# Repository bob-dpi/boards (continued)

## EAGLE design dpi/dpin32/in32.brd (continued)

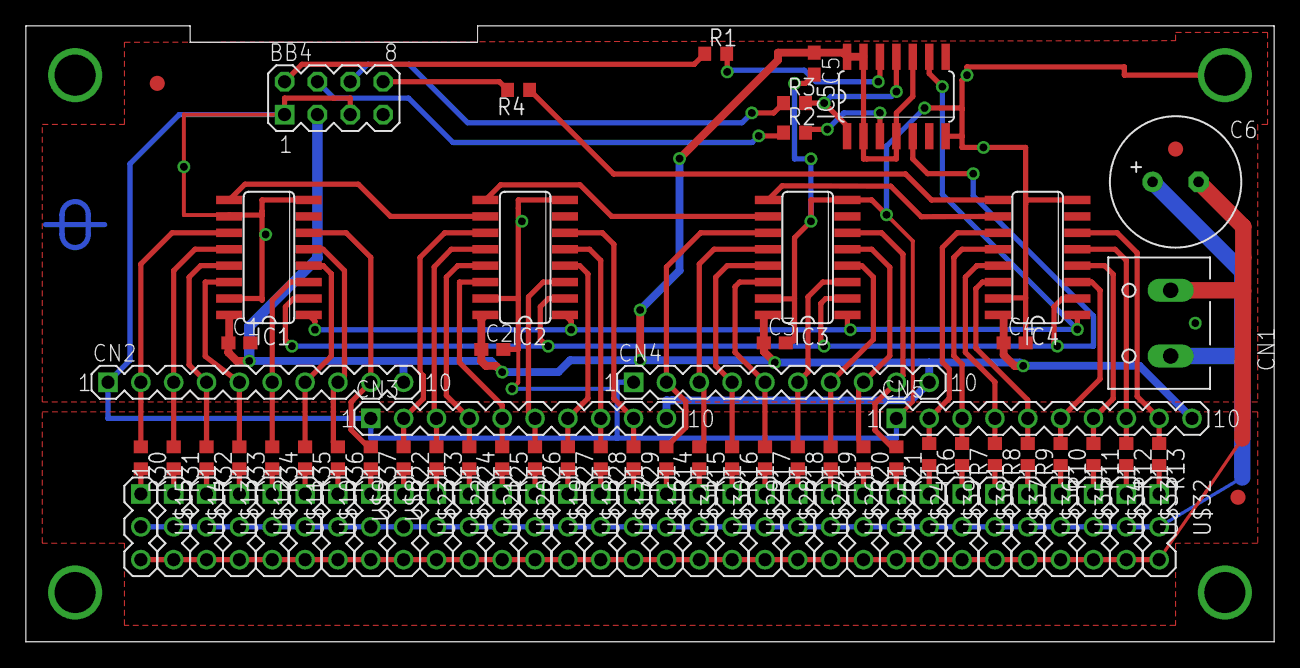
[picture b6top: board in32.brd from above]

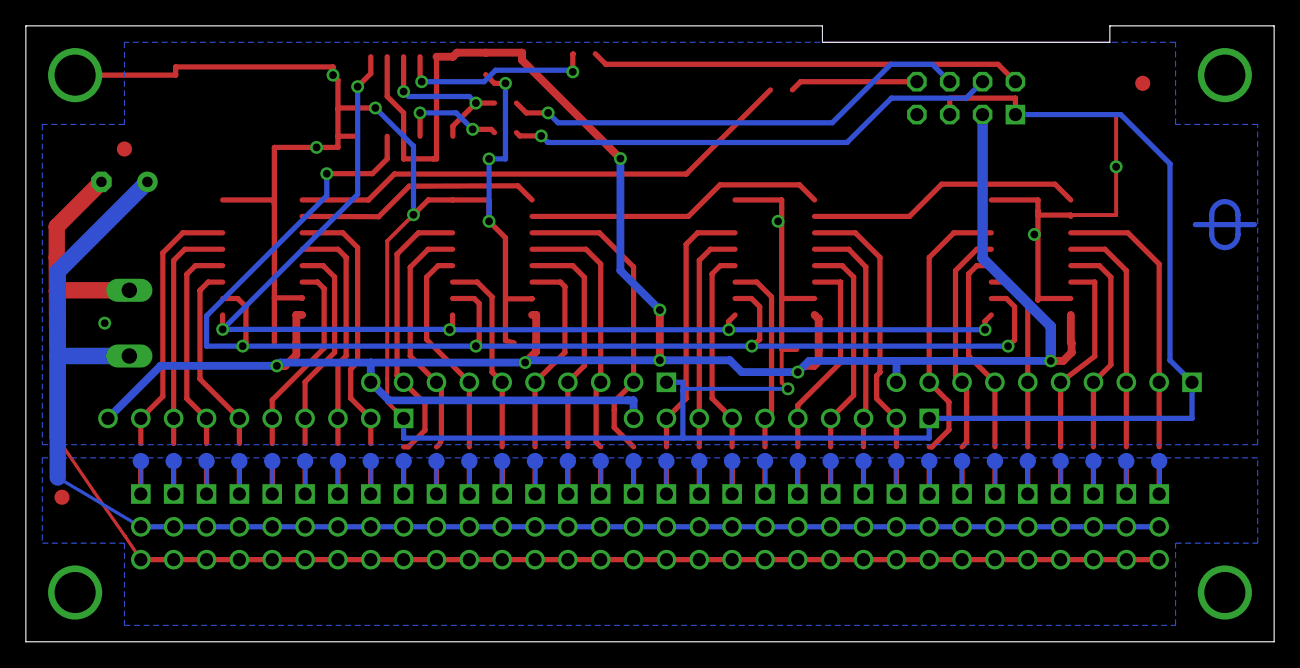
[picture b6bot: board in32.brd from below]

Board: 2 copper layers, 96.5 x 47.6 mm, 124 parts (33 on the bottom side), 81 nets.

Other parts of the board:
E$1, E$2, E$3, E$4, E$5, E$7, E$8, E$9, E$10, E$11, E$12, E$13, E$14, E$15, E$16, E$17, E$18, E$19, E$20, E$21, E$22, E$23, E$24, E$26, E$27, E$28, E$29, E$30, E$31, E$32, E$33, E$34: TEST-POINT
E$25: P_FRAME
U$1: P_FRAME
U$4, U$5, U$6: FIDUCIAL
U$7: DPI-1

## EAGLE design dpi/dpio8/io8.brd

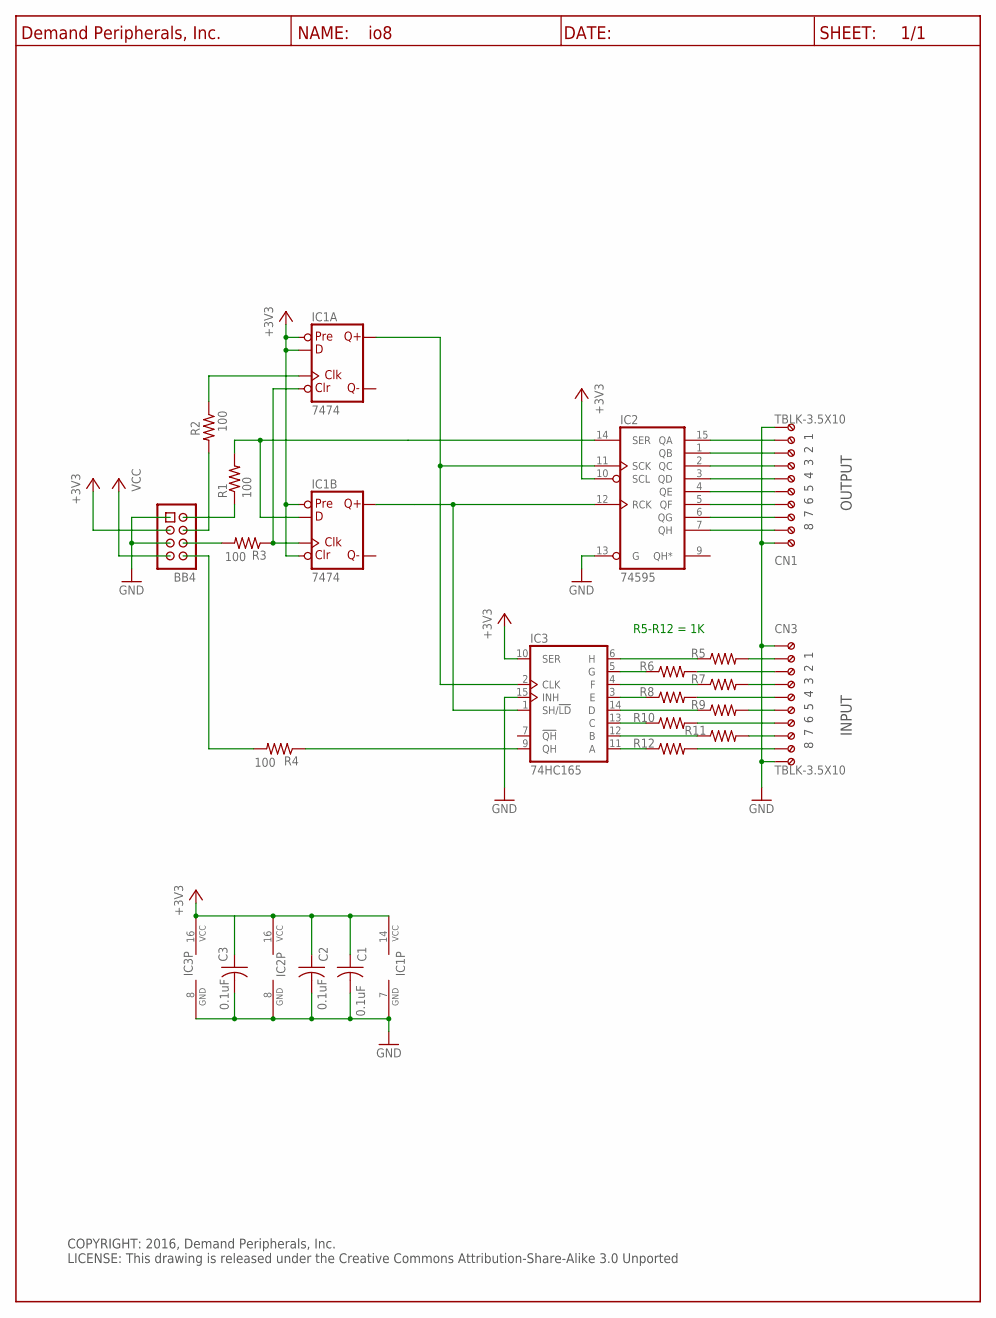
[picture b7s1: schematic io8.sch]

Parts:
BB4: Hdr_4x2; HDR-4X2
C1, C2, C3: 0.1uF; C0603
CN1, CN3: TBLK-3.5X10
IC1: 7474; SO14
IC2: 74595; SO16
IC3: 74HC165; SO16
R1, R2, R3, R4: 100; R0603
R5, R6, R7, R8, R9, R10, R11, R12: R1K_R0603; R0603
U$5: DP_FRAME_P; P_FRAME

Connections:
+3V3: BB4.3, C1.1, C2.1, C3.1, IC1.2 (D), IC1.4 (PRE), IC1.10 (PRE), IC1.13 (CLR), IC1.14 (VCC), IC2.10 (SCL), IC2.16 (VCC), IC3.10 (SER), IC3.16 (VCC)
GND: BB4.1, BB4.5, C1.2, C2.2, C3.2, CN1.1 (KL), CN1.10 (KL9), CN3.1 (KL), CN3.10 (KL9), IC1.7 (GND), IC2.8 (GND), IC2.13 (G), IC3.8 (GND), IC3.15 (INH)
unnamed: BB4.2, R1.1
unnamed: BB4.8, R4.2
unnamed: CN3.9 (KL8), R12.2
unnamed: CN3.8 (KL7), R11.2
unnamed: CN3.7 (KL6), R10.2
unnamed: IC1.12 (D), IC2.14 (SER), R1.2
unnamed: CN3.6 (KL5), R9.2
unnamed: CN3.5 (KL4), R8.2
unnamed: CN3.4 (KL3), R7.2
unnamed: CN3.3 (KL2), R6.2
unnamed: CN3.2 (KL1), R5.2
unnamed: IC1.5 (Q), IC2.11 (SCK), IC3.2 (CLK)
unnamed: IC3.11 (A), R12.1
unnamed: CN1.2 (KL1), IC2.7 (QH)
unnamed: IC1.1 (CLR), IC1.11 (CLK), R3.1
unnamed: BB4.4, R2.2
unnamed: IC1.3 (CLK), R2.1
unnamed: BB4.6, R3.2
unnamed: CN1.3 (KL2), IC2.6 (QG)
unnamed: CN1.4 (KL3), IC2.5 (QF)
unnamed: CN1.5 (KL4), IC2.4 (QE)
unnamed: CN1.6 (KL5), IC2.3 (QD)
unnamed: CN1.7 (KL6), IC2.2 (QC)
unnamed: CN1.8 (KL7), IC2.1 (QB)
unnamed: CN1.9 (KL8), IC2.15 (QA)
unnamed: IC3.9 (QH), R4.1
unnamed: IC3.12 (B), R11.1
unnamed: IC1.9 (Q), IC2.12 (RCK), IC3.1 (SH/!LD)
unnamed: IC3.13 (C), R10.1
unnamed: IC3.14 (D), R9.1
unnamed: IC3.3 (E), R8.1
unnamed: IC3.4 (F), R7.1
unnamed: IC3.5 (G), R6.1
unnamed: IC3.6 (H), R5.1
VCC: BB4.7

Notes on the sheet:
COPYRIGHT: 2016, Demand Peripherals, Inc. LICENSE: This drawing is released under the Creative Commons Attribution-Share-Alike 3.0 Unported
OUTPUT
INPUT
R5-R12 = 1K

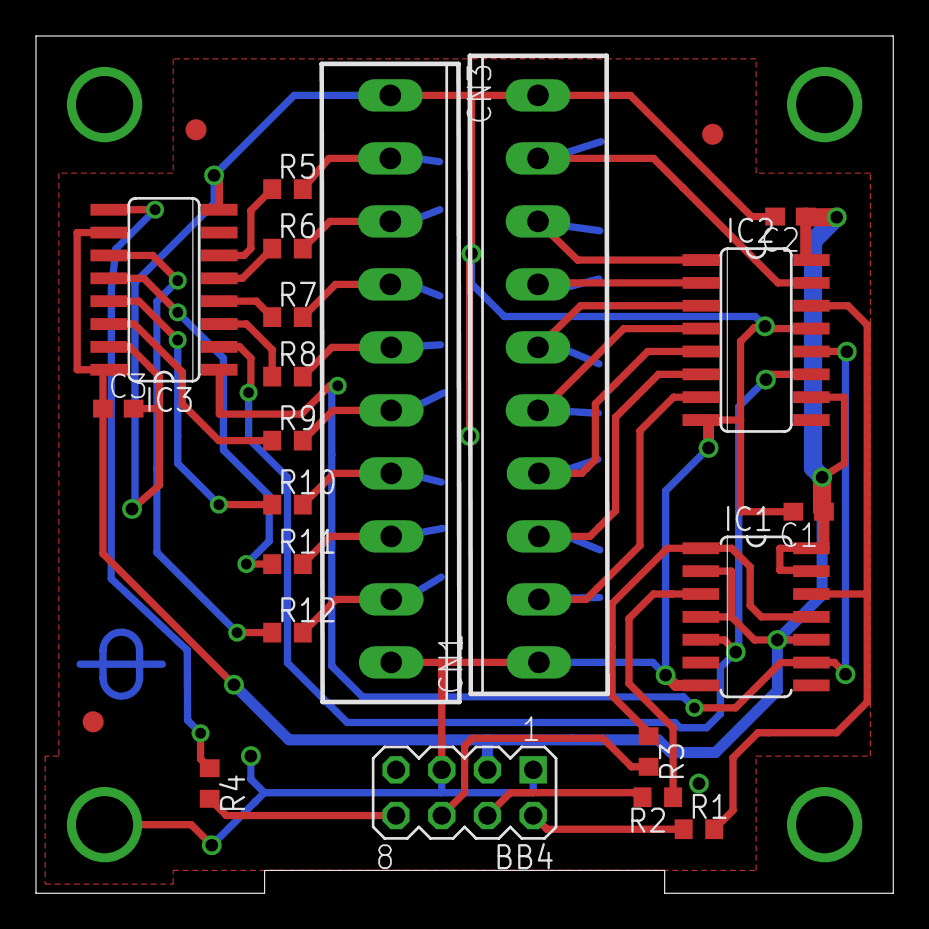
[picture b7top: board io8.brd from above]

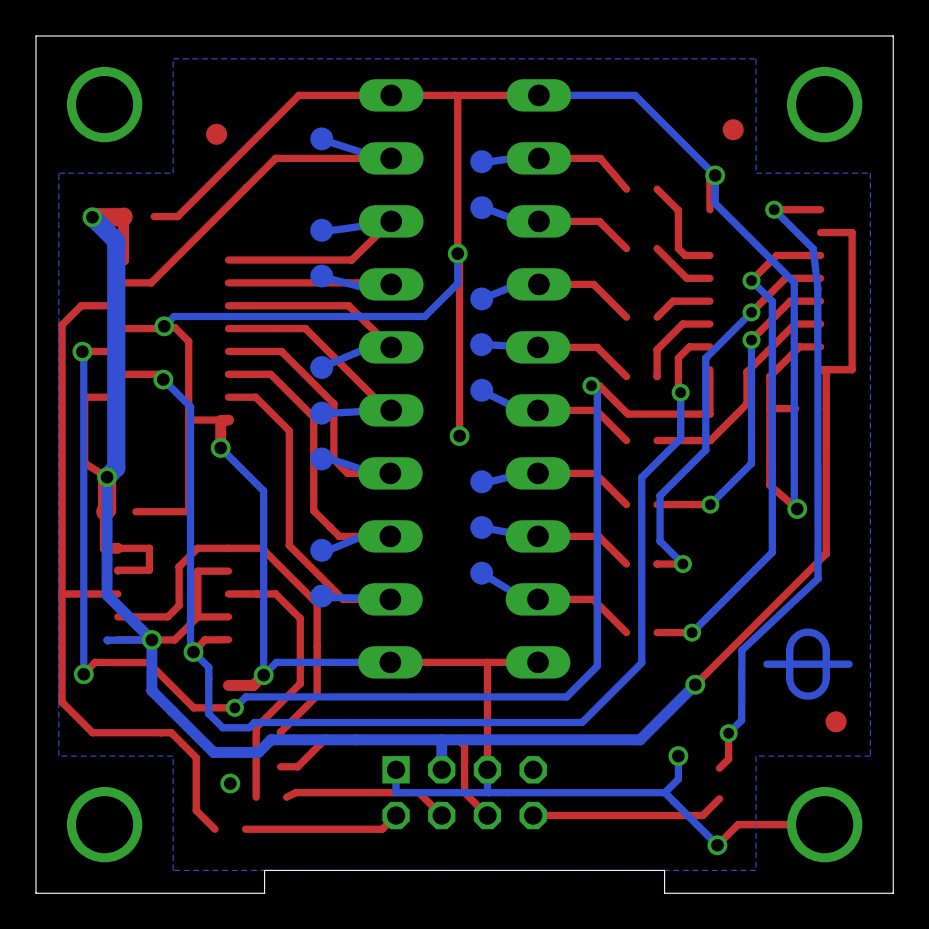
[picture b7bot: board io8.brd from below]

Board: 2 copper layers, 47.6 x 47.6 mm, 42 parts (17 on the bottom side), 36 nets.

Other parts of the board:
E$2, E$4, E$5, E$6, E$7, E$8, E$9, E$10, E$11, E$12, E$13, E$14, E$15, E$16, E$18, E$19: TEST-POINT
U$1, U$3, U$4: FIDUCIAL
U$6: DPI-1

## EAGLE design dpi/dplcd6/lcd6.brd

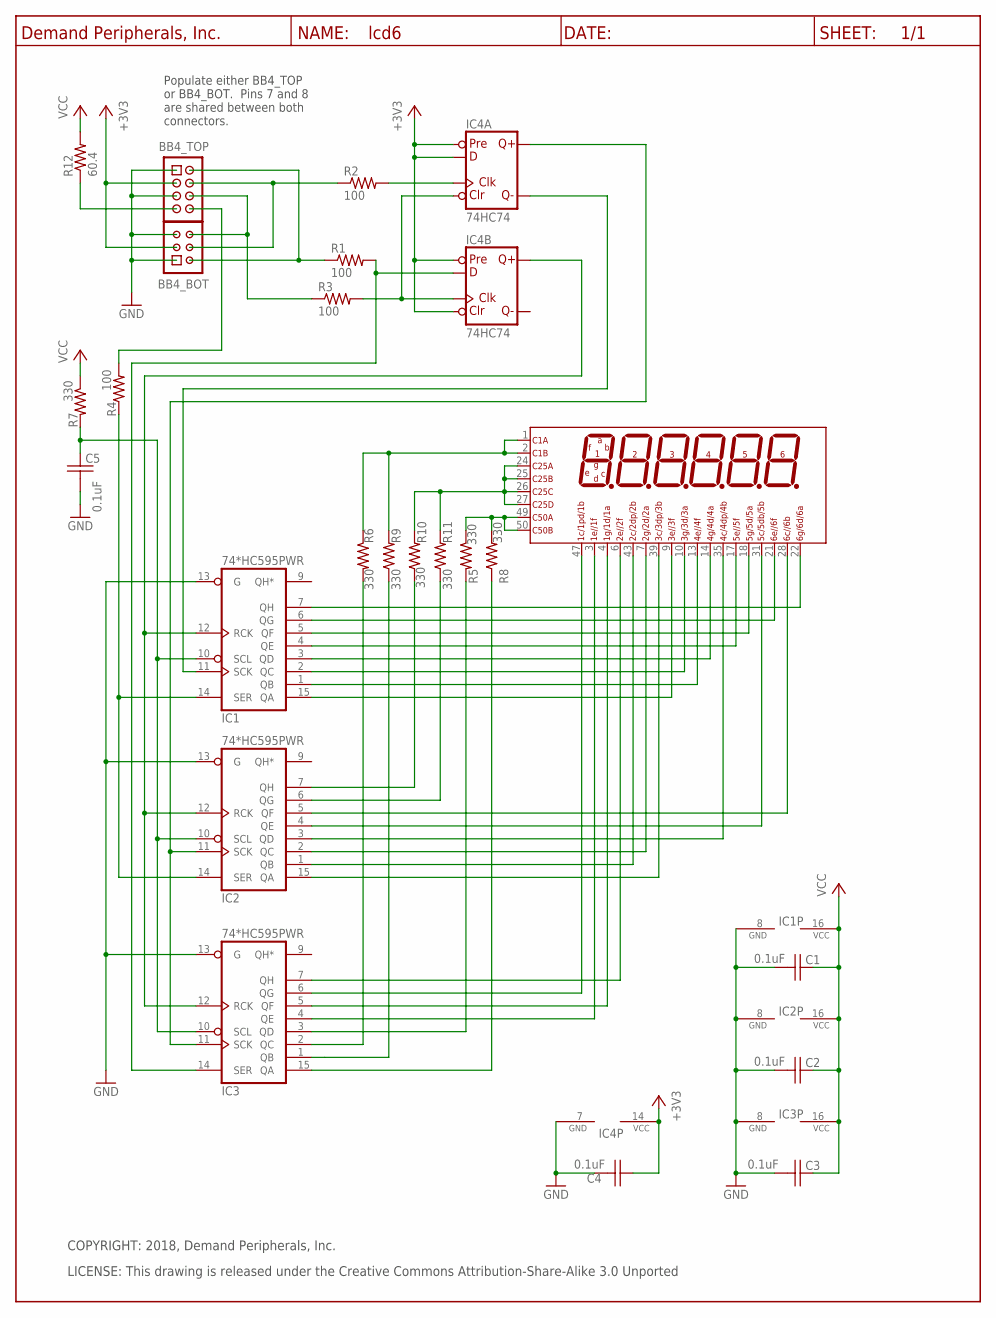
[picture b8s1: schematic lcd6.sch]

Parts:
BB4_BOT: HDR-3X2
BB4_TOP: Keyed_Pin_Header_4x2(0.1"x0.1"); HDR-4X2
C1, C2, C3, C4, C5: 0.1uF; C0603
DISP1: LCD6
IC1, IC2, IC3: 74*HC595PWR; SO16
IC4: 74HC74; SO14
R1, R2, R3, R4: 100; R0603
R5, R6, R7, R8, R9, R10, R11: 330; R0603
R12: 60.4; R0603
U$1: DP_FRAME_P; P_FRAME

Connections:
3A: IC3.15 (QA), R8.1
3B: IC3.1 (QB), R9.1
+3V3: BB4_BOT.3, BB4_TOP.3, C4.1, IC4.2 (D), IC4.4 (PRE), IC4.10 (PRE), IC4.13 (CLR), IC4.14 (VCC)
GND: BB4_BOT.1, BB4_BOT.5, BB4_TOP.1, BB4_TOP.5, C1.2, C2.2, C3.2, C4.2, C5.2, IC1.8 (GND), IC1.13 (G), IC2.8 (GND), IC2.13 (G), IC3.8 (GND), IC3.13 (G), IC4.7 (GND)
unnamed: BB4_TOP.8, R4.2
unnamed: IC3.3 (QD), R5.2
unnamed: IC1.12 (RCK), IC2.12 (RCK), IC3.12 (RCK), IC4.9 (Q)
unnamed: IC2.11 (SCK), IC3.11 (SCK), IC4.5 (Q)
unnamed: DISP1.3, IC3.4 (QE)
unnamed: DISP1.4, IC3.5 (QF)
unnamed: IC3.2 (QC), R6.2
unnamed: DISP1.24, DISP1.25, DISP1.26, DISP1.27, R10.2, R11.2
unnamed: DISP1.47, IC3.6 (QG)
unnamed: DISP1.6, IC3.7 (QH)
unnamed: IC2.7 (QH), R10.1
unnamed: IC2.6 (QG), R11.1
unnamed: DISP1.22, IC1.7 (QH)
unnamed: DISP1.21, IC1.6 (QG)
unnamed: DISP1.18, IC1.5 (QF)
unnamed: DISP1.17, IC1.4 (QE)
unnamed: DISP1.14, IC1.3 (QD)
unnamed: DISP1.13, IC1.1 (QB)
unnamed: DISP1.10, IC1.2 (QC)
unnamed: DISP1.28, IC2.5 (QF)
unnamed: DISP1.31, IC2.4 (QE)
unnamed: DISP1.35, IC2.3 (QD)
unnamed: DISP1.9, IC1.15 (QA)
unnamed: DISP1.39, IC2.15 (QA)
unnamed: DISP1.7, IC2.2 (QC)
unnamed: BB4_BOT.2, BB4_TOP.2, R1.1
unnamed: DISP1.43, IC2.1 (QB)
unnamed: IC4.3 (CLK), R2.2
unnamed: IC3.14 (SER), IC4.12 (D), R1.2
unnamed: IC4.1 (CLR), IC4.11 (CLK), R3.2
unnamed: IC1.14 (SER), IC2.14 (SER), R4.1
unnamed: BB4_BOT.6, BB4_TOP.6, R3.1
unnamed: IC1.11 (SCK), IC4.6 (!Q)
unnamed: BB4_BOT.4, BB4_TOP.4, R2.1
unnamed: DISP1.49, DISP1.50, R5.1, R8.2
unnamed: C5.1, IC1.10 (SCL), IC2.10 (SCL), IC3.10 (SCL), R7.2
unnamed: DISP1.1, DISP1.2, R6.1, R9.2
unnamed: BB4_TOP.7, R12.1
VCC: C1.1, C2.1, C3.1, IC1.16 (VCC), IC2.16 (VCC), IC3.16 (VCC), R7.1, R12.2

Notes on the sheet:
COPYRIGHT: 2018, Demand Peripherals, Inc.
LICENSE: This drawing is released under the Creative Commons Attribution-Share-Alike 3.0 Unported
Populate either BB4_TOP or BB4_BOT. Pins 7 and 8 are shared between both connectors.

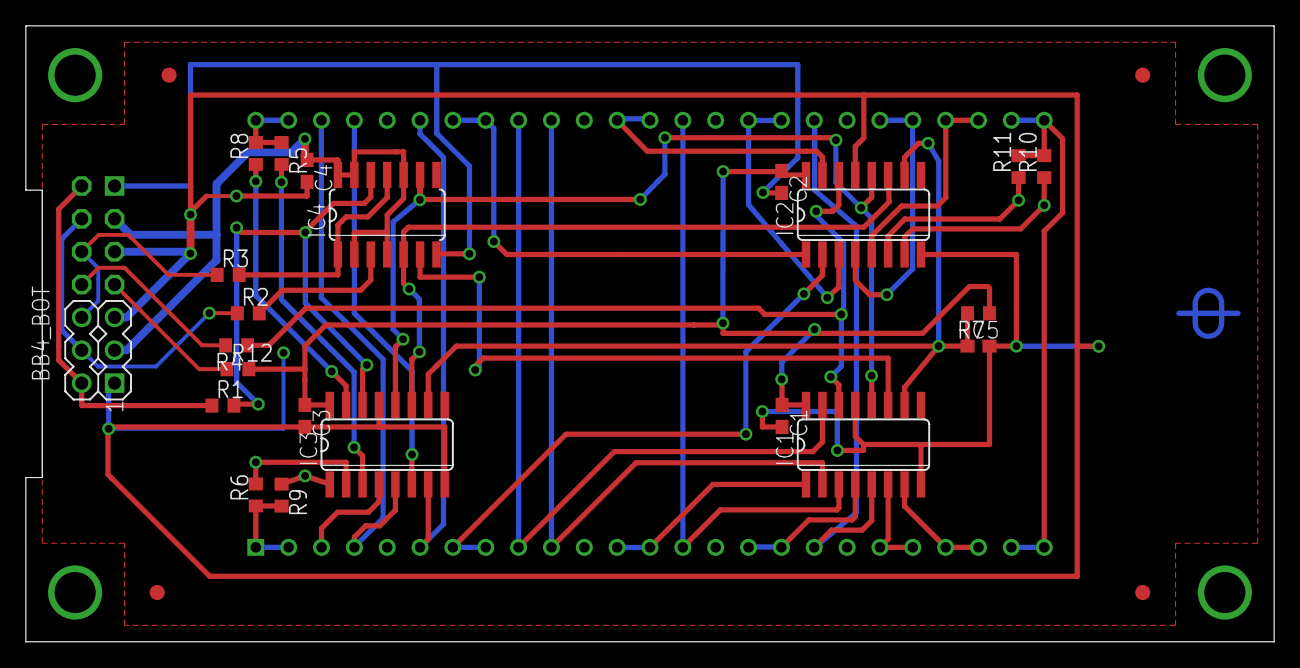
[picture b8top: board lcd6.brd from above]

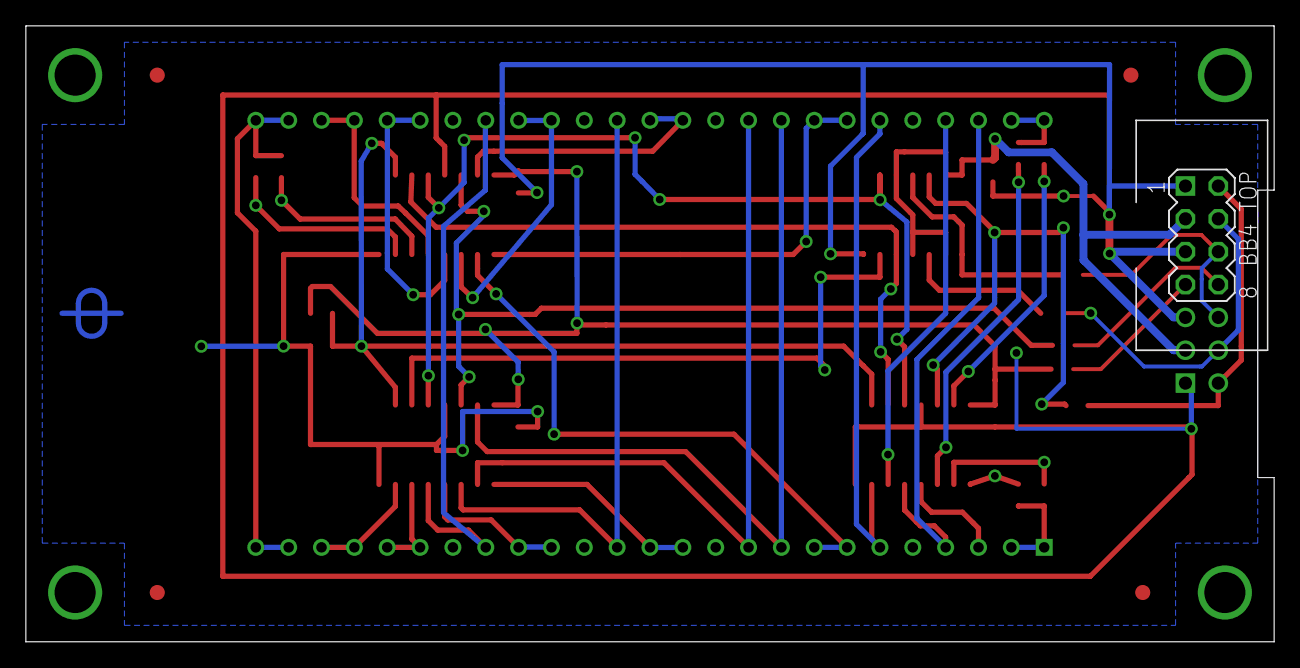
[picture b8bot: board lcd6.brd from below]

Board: 2 copper layers, 96.5 x 47.6 mm, 30 parts (2 on the bottom side), 43 nets.

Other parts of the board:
U$3, U$4, U$5, U$6: FIDUCIAL
U$7: DPI-1
